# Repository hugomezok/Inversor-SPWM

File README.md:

# Inversor-SPWM

Proyecto para la materia "Electrónica de Potencia" de la UTN-FRBA.  
En el contexto de aplicaciones de baja frecuencia, se desarrolló un inversor de 12V DC a 220V AC mediante modulación SPWM, junto con una investigación sobre dos tipos de núcleos de transformador para optimizar la generación de la señal senoidal.

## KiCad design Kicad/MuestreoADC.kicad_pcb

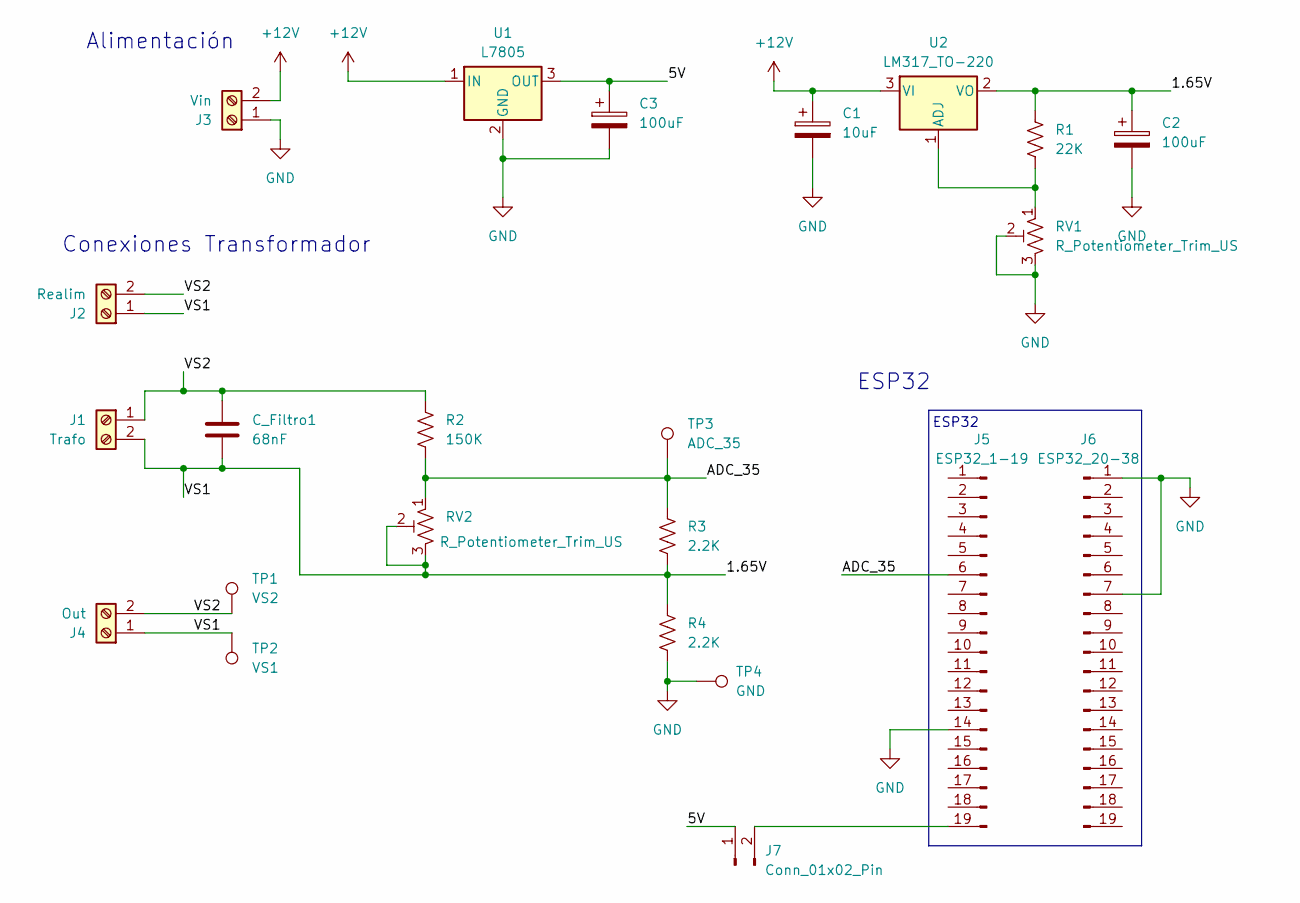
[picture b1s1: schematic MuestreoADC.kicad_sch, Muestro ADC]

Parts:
C1: 10uF; CP_Radial_D5.0mm_P2.50mm
C2, C3: 100uF; CP_Radial_D6.3mm_P2.50mm
C_Filtro1: 68nF; C_Rect_L9.0mm_W2.5mm_P7.50mm_MKT
J1: Trafo; TerminalBlock_RND_205-00276_1x02_P5.00mm_Vertical
J2: Realim; TerminalBlock_RND_205-00276_1x02_P5.00mm_Vertical
J3: Vin; TerminalBlock_RND_205-00276_1x02_P5.00mm_Vertical
J4: Out; TerminalBlock_RND_205-00276_1x02_P5.00mm_Vertical
J5: ESP32_1-19; PinHeader_1x19_P2.54mm_Vertical
J6: ESP32_20-38; PinHeader_1x19_P2.54mm_Vertical
J7: Conn_01x02_Pin; PinHeader_1x02_P2.54mm_Vertical
R1: 22K; R_Axial_DIN0207_L6.3mm_D2.5mm_P10.16mm_Horizontal
R2: 150K; R_Axial_DIN0207_L6.3mm_D2.5mm_P10.16mm_Horizontal
R3, R4: 2.2K; R_Axial_DIN0207_L6.3mm_D2.5mm_P10.16mm_Horizontal
RV1, RV2: R_Potentiometer_Trim_US; Potentiometer_Vishay_T93YA_Vertical
TP1: VS2; Pin_D1.0mm_L10.0mm
TP2: VS1; Pin_D1.0mm_L10.0mm
TP3: ADC_35; Pin_D1.0mm_L10.0mm
TP4: GND; Pin_D1.0mm_L10.0mm
U1: L7805; TO-220-3_Vertical
U2: LM317_TO-220; TO-220-3_Vertical

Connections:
+12V: C1.1, J3.2, U1.1 (IN), U2.3 (VI)
/1.65V: C2.1, C_Filtro1.2, J1.2, J2.1, J4.1, R1.1, R3.2, R4.1, RV2.2, RV2.3, TP2.1, U2.2 (VO)
/5V: C3.1, J7.1, U1.3 (OUT)
/ADC_35: J5.6, R2.2, R3.1, RV2.1, TP3.1
/VS2: C_Filtro1.1, J1.1, J2.2, J4.2, R2.1, TP1.1
GND: C1.2, C2.2, C3.2, J3.1, J5.14, J6.1, J6.7, R4.2, RV1.2, RV1.3, TP4.1, U1.2 (GND)
unnamed: J5.19, J7.2
unnamed: R1.2, RV1.1, U2.1 (ADJ)

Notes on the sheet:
Alimentación
ESP32
ESP32
Conexiones Transformador

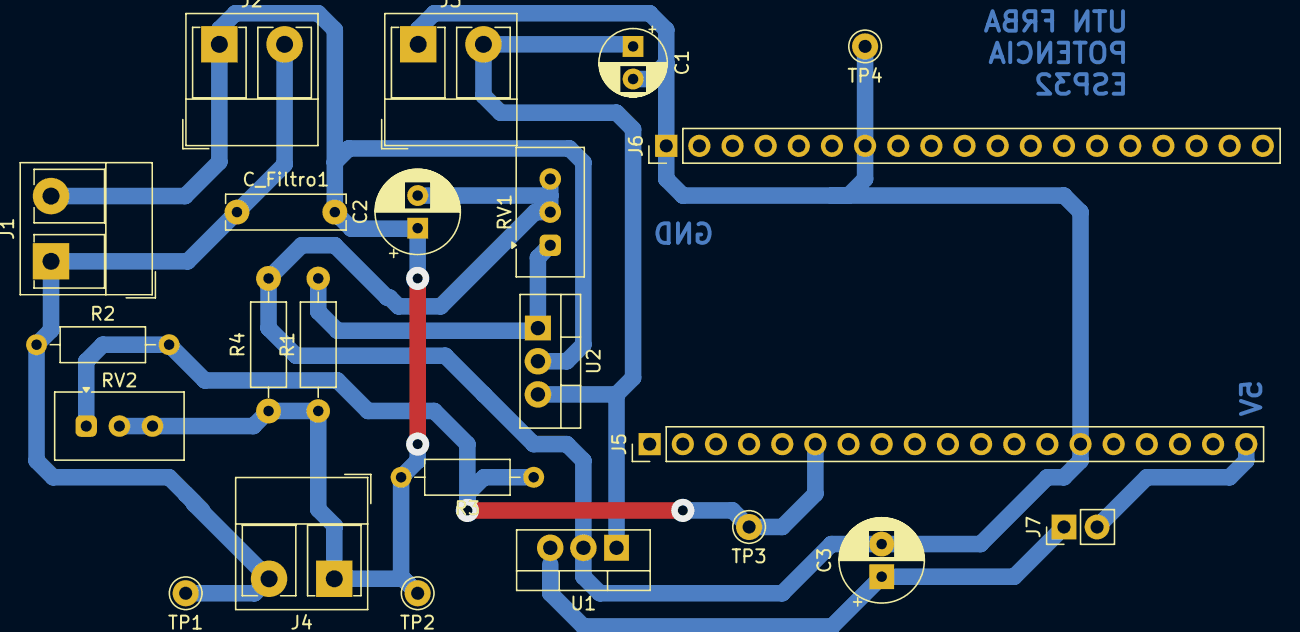
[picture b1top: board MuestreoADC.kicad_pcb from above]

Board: 2 copper layers, 23 parts (0 on the bottom side), 8 nets.

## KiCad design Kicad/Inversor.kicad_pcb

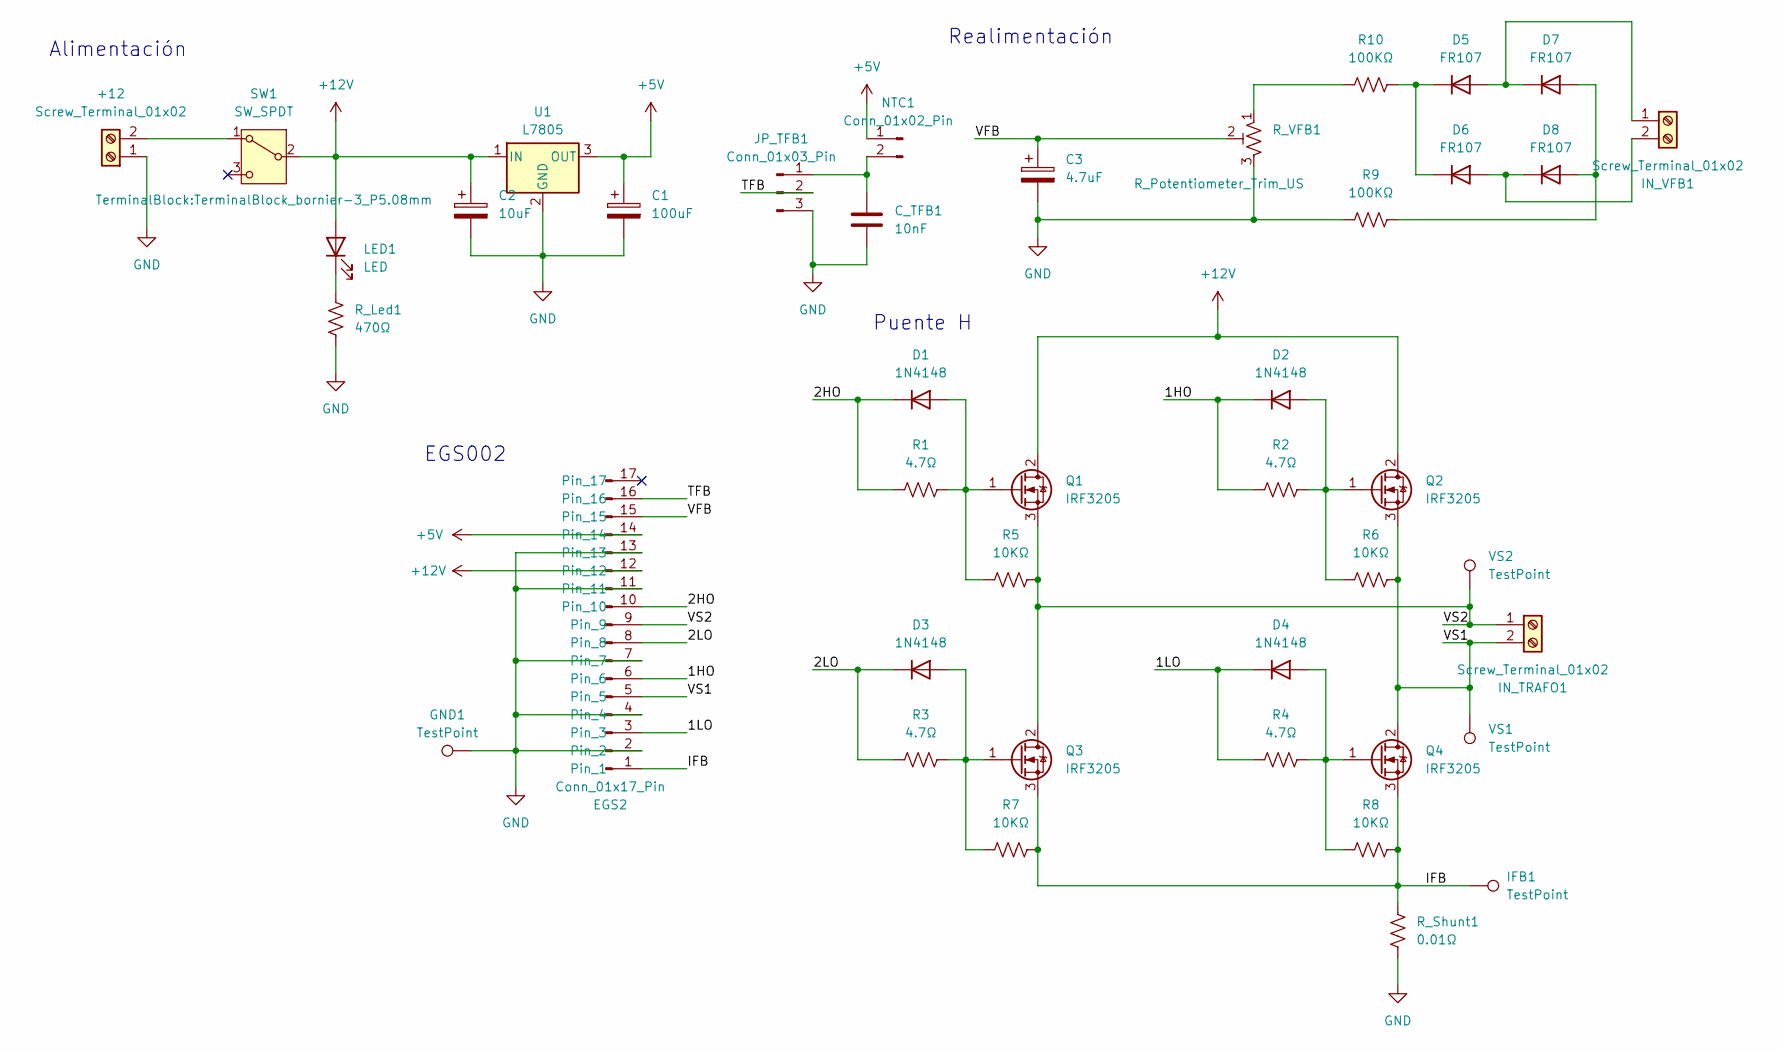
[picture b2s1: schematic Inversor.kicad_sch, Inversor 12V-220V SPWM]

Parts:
+12: Screw_Terminal_01x02; TerminalBlock_RND_205-00276_1x02_P5.00mm_Vertical
C1: 100uF; CP_Radial_D8.0mm_P3.80mm
C2: 10uF; CP_Radial_D5.0mm_P2.50mm
C3: 4.7uF; CP_Radial_D5.0mm_P2.50mm
C_TFB1: 10nF; C_Disc_D3.0mm_W2.0mm_P2.50mm
D1, D2, D3, D4: 1N4148; D_DO-35_SOD27_P7.62mm_Horizontal
D5, D6, D7, D8: FR107; D_DO-15_P10.16mm_Horizontal
EGS2: Conn_01x17_Pin; PinHeader_1x17_P2.54mm_Vertical
GND1: TestPoint; Pin_D1.0mm_L10.0mm
IFB1: TestPoint; Pin_D1.0mm_L10.0mm
IN_TRAFO1: Screw_Terminal_01x02; TerminalBlock_RND_205-00276_1x02_P5.00mm_Vertical
IN_VFB1: Screw_Terminal_01x02; TerminalBlock_RND_205-00276_1x02_P5.00mm_Vertical
JP_TFB1: Conn_01x03_Pin; PinHeader_1x03_P1.27mm_Vertical
LED1: LED; LED_D5.0mm
NTC1: Conn_01x02_Pin; PinHeader_1x02_P1.27mm_Vertical
Q1, Q2, Q3, Q4: IRF3205; TO-220-3_Vertical
R1, R2, R3, R4: 4.7Ω; R_Axial_DIN0207_L6.3mm_D2.5mm_P10.16mm_Horizontal
R5, R6, R7, R8: 10KΩ; R_Axial_DIN0207_L6.3mm_D2.5mm_P10.16mm_Horizontal
R9, R10: 100KΩ; R_Axial_DIN0207_L6.3mm_D2.5mm_P10.16mm_Horizontal
R_Led1: 470Ω; R_Axial_DIN0207_L6.3mm_D2.5mm_P10.16mm_Horizontal
R_Shunt1: 0.01Ω; R_Axial_DIN0207_L6.3mm_D2.5mm_P5.08mm_Vertical
R_VFB1: R_Potentiometer_Trim_US; Potentiometer_Vishay_T93YA_Vertical
SW1: SW_SPDT; TerminalBlock_bornier-3_P5.08mm
U1: L7805; TO-220-3_Vertical
VS1, VS2: TestPoint; Pin_D1.0mm_L10.0mm

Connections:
+5V: C1.1, EGS2.14, NTC1.1, U1.3 (OUT)
+12V: C2.1, EGS2.12, LED1.2 (A), Q1.2 (D), Q2.2 (D), SW1.2 (B), U1.1 (IN)
/1HO: D2.1 (K), EGS2.6, R2.1
/1LO: D4.1 (K), EGS2.3, R4.1
/2HO: D1.1 (K), EGS2.10, R1.1
/2LO: D3.1 (K), EGS2.8, R3.1
/IFB: EGS2.1, IFB1.1, Q3.3 (S), Q4.3 (S), R7.2, R8.2, R_Shunt1.1
/TFB: EGS2.16, JP_TFB1.2
/VFB: C3.1, EGS2.15, R_VFB1.2
/VS1: EGS2.5, IN_TRAFO1.2, Q2.3 (S), Q4.2 (D), R6.2, VS1.1
/VS2: EGS2.9, IN_TRAFO1.1, Q1.3 (S), Q3.2 (D), R5.2, VS2.1
GND: +12.1, C1.2, C2.2, C3.2, C_TFB1.2, EGS2.2, EGS2.4, EGS2.7, EGS2.11, EGS2.13, GND1.1, JP_TFB1.3, R9.1, R_Led1.1, R_Shunt1.2, R_VFB1.3, U1.2 (GND)
unnamed: +12.2, SW1.1 (A)
unnamed: D1.2 (A), Q1.1 (G), R1.2, R5.1
unnamed: D2.2 (A), Q2.1 (G), R2.2, R6.1
unnamed: D3.2 (A), Q3.1 (G), R3.2, R7.1
unnamed: D4.2 (A), Q4.1 (G), R4.2, R8.1
unnamed: D5.2 (A), D7.1 (K), IN_VFB1.1
unnamed: D5.1 (K), D6.1 (K), R10.2
unnamed: D6.2 (A), D8.1 (K), IN_VFB1.2
unnamed: D7.2 (A), D8.2 (A), R9.2
unnamed: C_TFB1.1, JP_TFB1.1, NTC1.2
unnamed: LED1.1 (K), R_Led1.2
unnamed: R10.1, R_VFB1.1

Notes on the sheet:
Puente H
Alimentación
EGS002
Realimentación

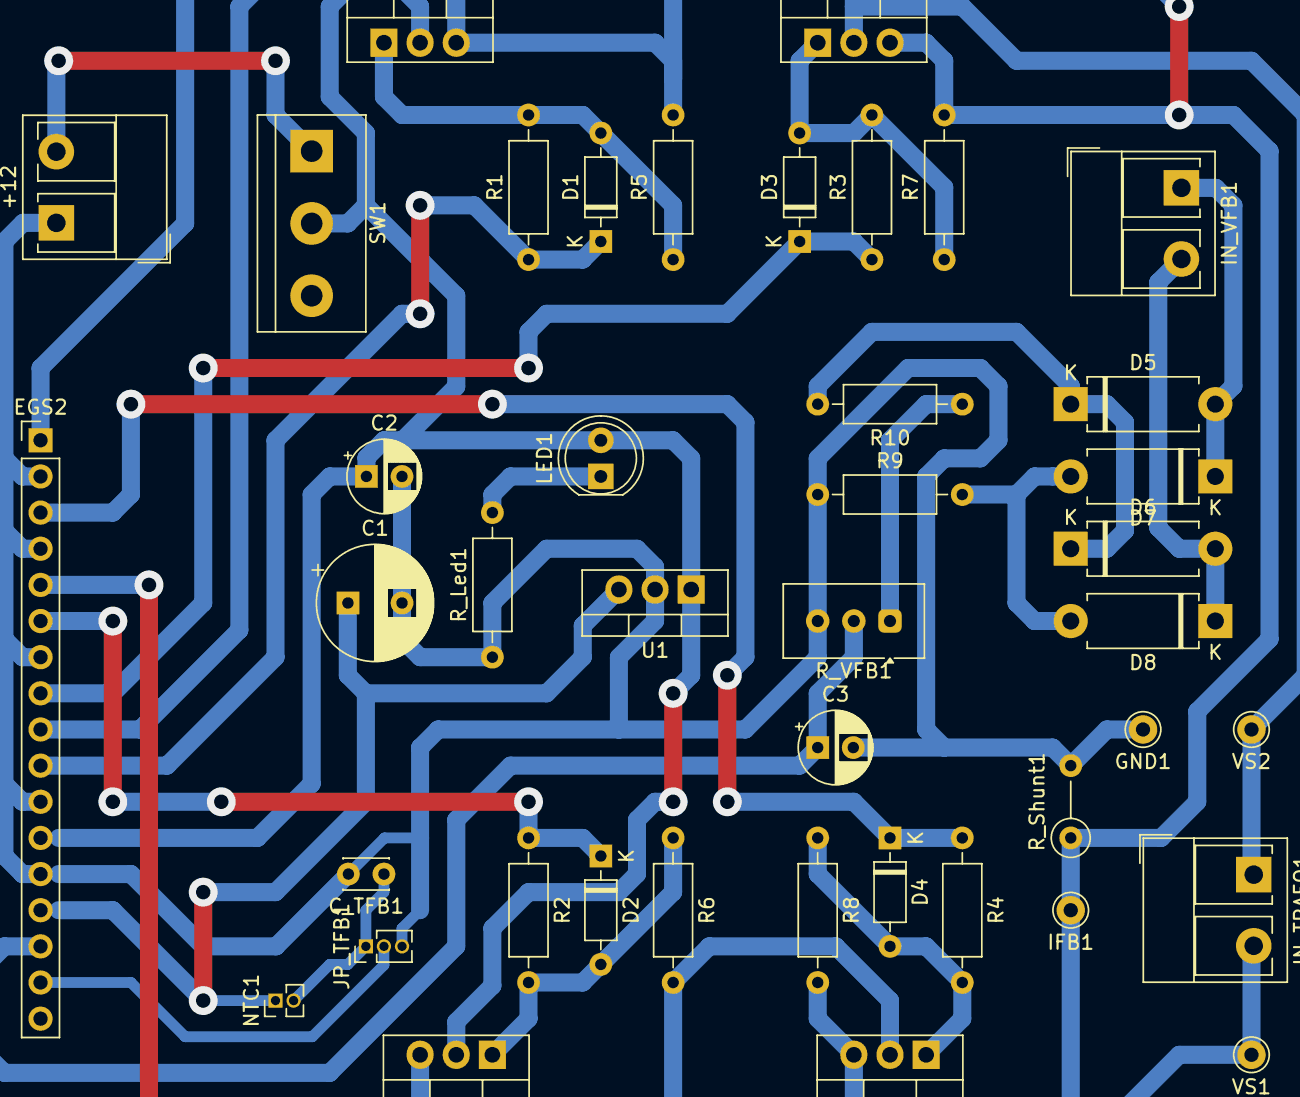
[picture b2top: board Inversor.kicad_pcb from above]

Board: 2 copper layers, 42 parts (0 on the bottom side), 24 nets.

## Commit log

2025-04-03 Commit de la documentación del proyecto
